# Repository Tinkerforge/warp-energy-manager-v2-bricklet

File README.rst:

WARP Energy Manager Bricklet 2.0
================================

**This Bricklet is currently in development.**

This repository contains the firmware source code and the hardware design
files. The documentation generator configs can be found at
https://github.com/Tinkerforge/generators

.. BEGIN WARP REPOSITORIES (managed block, generated from esp32-firmware/repo_overview.rst - do not edit by hand, run update_repo_overview.py instead)

WARP Repositories
-----------------

This is an overview of all repositories that make up the WARP Charger and
WARP Energy Manager ecosystem.

Please report **any** issue concerning WARP hard- or software in the
`esp32-firmware`_ repository, no matter which repository it originates from.

Software
~~~~~~~~

- `esp32-firmware`_ - Source code of the ESP32 firmware shared between all WARP Chargers and Energy Managers

Libraries used by the firmware:

- `tfjson`_ - SAX style JSON serializer and deserializer
- `tfnetwork`_ - Modbus TCP server and client implementation
- `tfocpp`_ - OCPP 1.6 implementation
- `tftools`_ - Miscellaneous tools and helpers

Remote access:

- `esp32-remote-access`_ - Source code of the my.warp-charger.com remote access server

Documentation, tools and integrations:

- `warp-charger`_ - Source code of (docs.)warp-charger.com and the printed manual, released firmwares, datasheets and documents, as well as some tools and hardware design files
- `api.warp-charger.com`_ - Serves APIs that are used by WARP Chargers to obtain relevant public information like day ahead prices
- `vislog.warp-charger.com`_ - Visualizes WARP Charger logs and EVSE debug protocols
- `dbus-warp-charger`_ - Integrates WARP Chargers into a Victron Energy Venus OS device (e.g. Cerbo GX)

WARP Charger Hardware
~~~~~~~~~~~~~~~~~~~~~~

WARP4 Charger
"""""""""""""

*Current charger generation.*

- `warp-esp32-ethernet-v2-brick`_ - Hardware design files of the WARP ESP32 Ethernet Brick 2.0
- `warp-esp32-ethernet-v2-co-bricklet`_ - Firmware source code of the WARP ESP32 Ethernet 2.0 Co Bricklet (co-processor)
- `evse-v4-bricklet`_ - Hardware design files of the EVSE 4.0 Bricklet (firmware shared with the EVSE 2.0 Bricklet)
- `nfc-bricklet`_ - Firmware source code and hardware design files of the NFC Bricklet

WARP3 Charger
"""""""""""""

- `warp-esp32-ethernet-brick`_ - Hardware design files of the WARP ESP32 Ethernet Brick
- `evse-v3-bricklet`_ - Hardware design files of the EVSE 3.0 Bricklet (firmware shared with the EVSE 2.0 Bricklet)
- `nfc-bricklet`_ - Firmware source code and hardware design files of the NFC Bricklet

WARP2 Charger
"""""""""""""

- `esp32-ethernet-brick`_ - Hardware design files of the ESP32 Ethernet Brick
- `evse-v2-bricklet`_ - Firmware source code and hardware design files of the EVSE 2.0 Bricklet
- `nfc-bricklet`_ - Firmware source code and hardware design files of the NFC Bricklet

WARP1 Charger
"""""""""""""

- `esp32-brick`_ - Hardware design files of the ESP32 Brick
- `evse-bricklet`_ - Firmware source code and hardware design files of the EVSE Bricklet
- `rs485-bricklet`_ - Firmware source code and hardware design files of the RS485 Bricklet

WARP Energy Manager Hardware
~~~~~~~~~~~~~~~~~~~~~~~~~~~~~~

WARP Energy Manager 2.0
"""""""""""""""""""""""

*Current energy manager generation.*

- `esp32-ethernet-brick`_ - Hardware design files of the ESP32 Ethernet Brick
- `warp-energy-manager-v2-bricklet`_ - Firmware source code and hardware design files of the WARP Energy Manager 2.0 Bricklet
- `warp-front-panel-bricklet`_ - Firmware source code and hardware design files of the WARP Front Panel Bricklet

WARP Energy Manager 1.0
"""""""""""""""""""""""

- `esp32-ethernet-brick`_ - Hardware design files of the ESP32 Ethernet Brick
- `warp-energy-manager-bricklet`_ - Firmware source code and hardware design files of the WARP Energy Manager Bricklet

Forked/patched projects
~~~~~~~~~~~~~~~~~~~~~~~~~

- `arduino-esp32`_
- `esp32-arduino-libs`_
- `WireGuard-ESP32-Arduino`_

.. Link targets: One definition per repository, keep in sync with the lists above.

.. _esp32-firmware: https://github.com/Tinkerforge/esp32-firmware
.. _tfjson: https://github.com/Tinkerforge/tfjson
.. _tfnetwork: https://github.com/Tinkerforge/tfnetwork
.. _tfocpp: https://github.com/Tinkerforge/tfocpp
.. _tftools: https://github.com/Tinkerforge/tftools
.. _esp32-remote-access: https://github.com/Tinkerforge/esp32-remote-access
.. _warp-charger: https://github.com/Tinkerforge/warp-charger
.. _api.warp-charger.com: https://github.com/Tinkerforge/api.warp-charger.com
.. _vislog.warp-charger.com: https://github.com/Tinkerforge/vislog.warp-charger.com
.. _dbus-warp-charger: https://github.com/Tinkerforge/dbus-warp-charger
.. _warp-esp32-ethernet-v2-brick: https://github.com/Tinkerforge/warp-esp32-ethernet-v2-brick
.. _warp-esp32-ethernet-v2-co-bricklet: https://github.com/Tinkerforge/warp-esp32-ethernet-v2-co-bricklet
.. _evse-v4-bricklet: https://github.com/Tinkerforge/evse-v4-bricklet
.. _nfc-bricklet: https://github.com/Tinkerforge/nfc-bricklet
.. _warp-esp32-ethernet-brick: https://github.com/Tinkerforge/warp-esp32-ethernet-brick
.. _evse-v3-bricklet: https://github.com/Tinkerforge/evse-v3-bricklet
.. _esp32-ethernet-brick: https://github.com/Tinkerforge/esp32-ethernet-brick
.. _evse-v2-bricklet: https://github.com/Tinkerforge/evse-v2-bricklet
.. _esp32-brick: https://github.com/Tinkerforge/esp32-brick
.. _evse-bricklet: https://github.com/Tinkerforge/evse-bricklet
.. _rs485-bricklet: https://github.com/Tinkerforge/rs485-bricklet
.. _warp-energy-manager-v2-bricklet: https://github.com/Tinkerforge/warp-energy-manager-v2-bricklet
.. _warp-front-panel-bricklet: https://github.com/Tinkerforge/warp-front-panel-bricklet
.. _warp-energy-manager-bricklet: https://github.com/Tinkerforge/warp-energy-manager-bricklet
.. _arduino-esp32: https://github.com/Tinkerforge/arduino-esp32
.. _esp32-arduino-libs: https://github.com/Tinkerforge/esp32-arduino-libs
.. _WireGuard-ESP32-Arduino: https://github.com/Tinkerforge/WireGuard-ESP32-Arduino

.. END WARP REPOSITORIES

Repository Content
------------------

software/:
 * examples/: Examples for all supported languages
 * build/: Compiled files
 * src/: Source code of firmware
 * Makefile: Makefile to build project

hardware/:
 * Contains KiCad project files and additionally schematics as PDF

datasheets/:
 * Contains datasheets for sensors and complex ICs that are used

Hardware
--------

The hardware is designed with the open source EDA Suite KiCad
(http://www.kicad.org). Before you are able to open the files,
you have to install the Tinkerforge kicad-libraries
(https://github.com/Tinkerforge/kicad-libraries). You can either clone
them directly in hardware/ or clone them in a separate folder and
symlink them into hardware/
(ln -s kicad_path/kicad-libraries project_path/hardware). After that you
can open the .pro file in hardware/ with KiCad and from there view and
modify the schematics and the PCB layout.

Software
--------

If you want to do your own Brick/Bricklet firmware development we highly
recommend that you use our build environment setup script and read the
tutorial (https://www.tinkerforge.com/en/doc/Tutorials/Tutorial_Build_Environment/Tutorial.html).

To compile the C code we recommend you to install the newest GNU Arm Embedded
Toolchain (https://launchpad.net/gcc-arm-embedded/+download).
You also need to install bricklib2 (https://github.com/Tinkerforge/bricklib2).

You can either clone it directly in software/src/ or clone it in a
separate folder and symlink it into software/src/
(ln -s bricklib_path/bricklib2 project_path/software/src/). Finally make sure to
have CMake installed (http://www.cmake.org/cmake/resources/software.html).

After that you can build the firmware by invoking make in software/.
The firmware (.zbin) can then be found in software/build/ and uploaded
with brickv (click button "Flashing" on start screen).

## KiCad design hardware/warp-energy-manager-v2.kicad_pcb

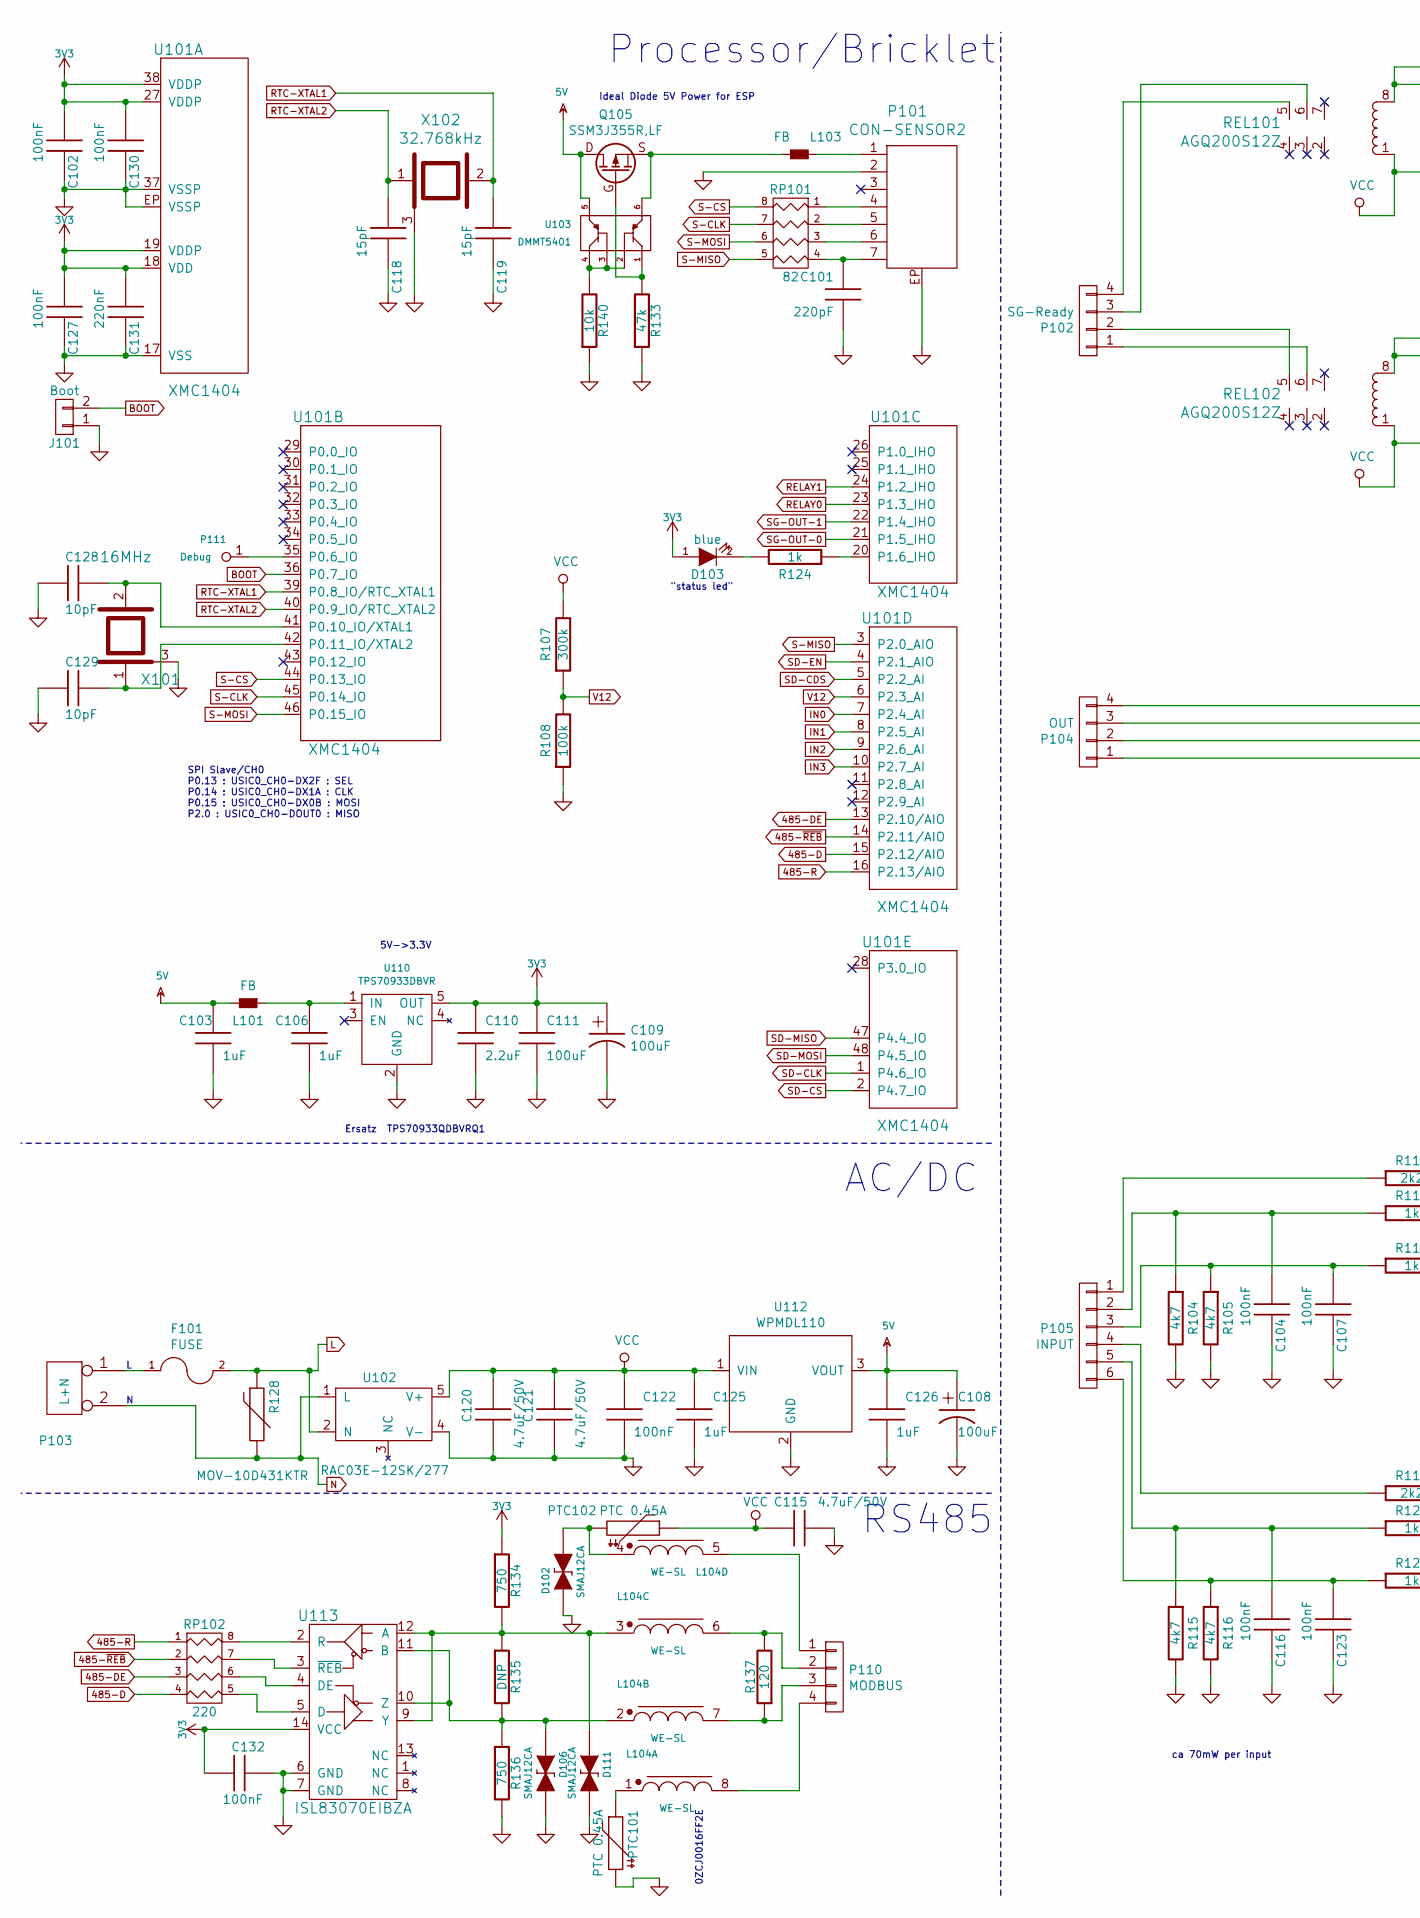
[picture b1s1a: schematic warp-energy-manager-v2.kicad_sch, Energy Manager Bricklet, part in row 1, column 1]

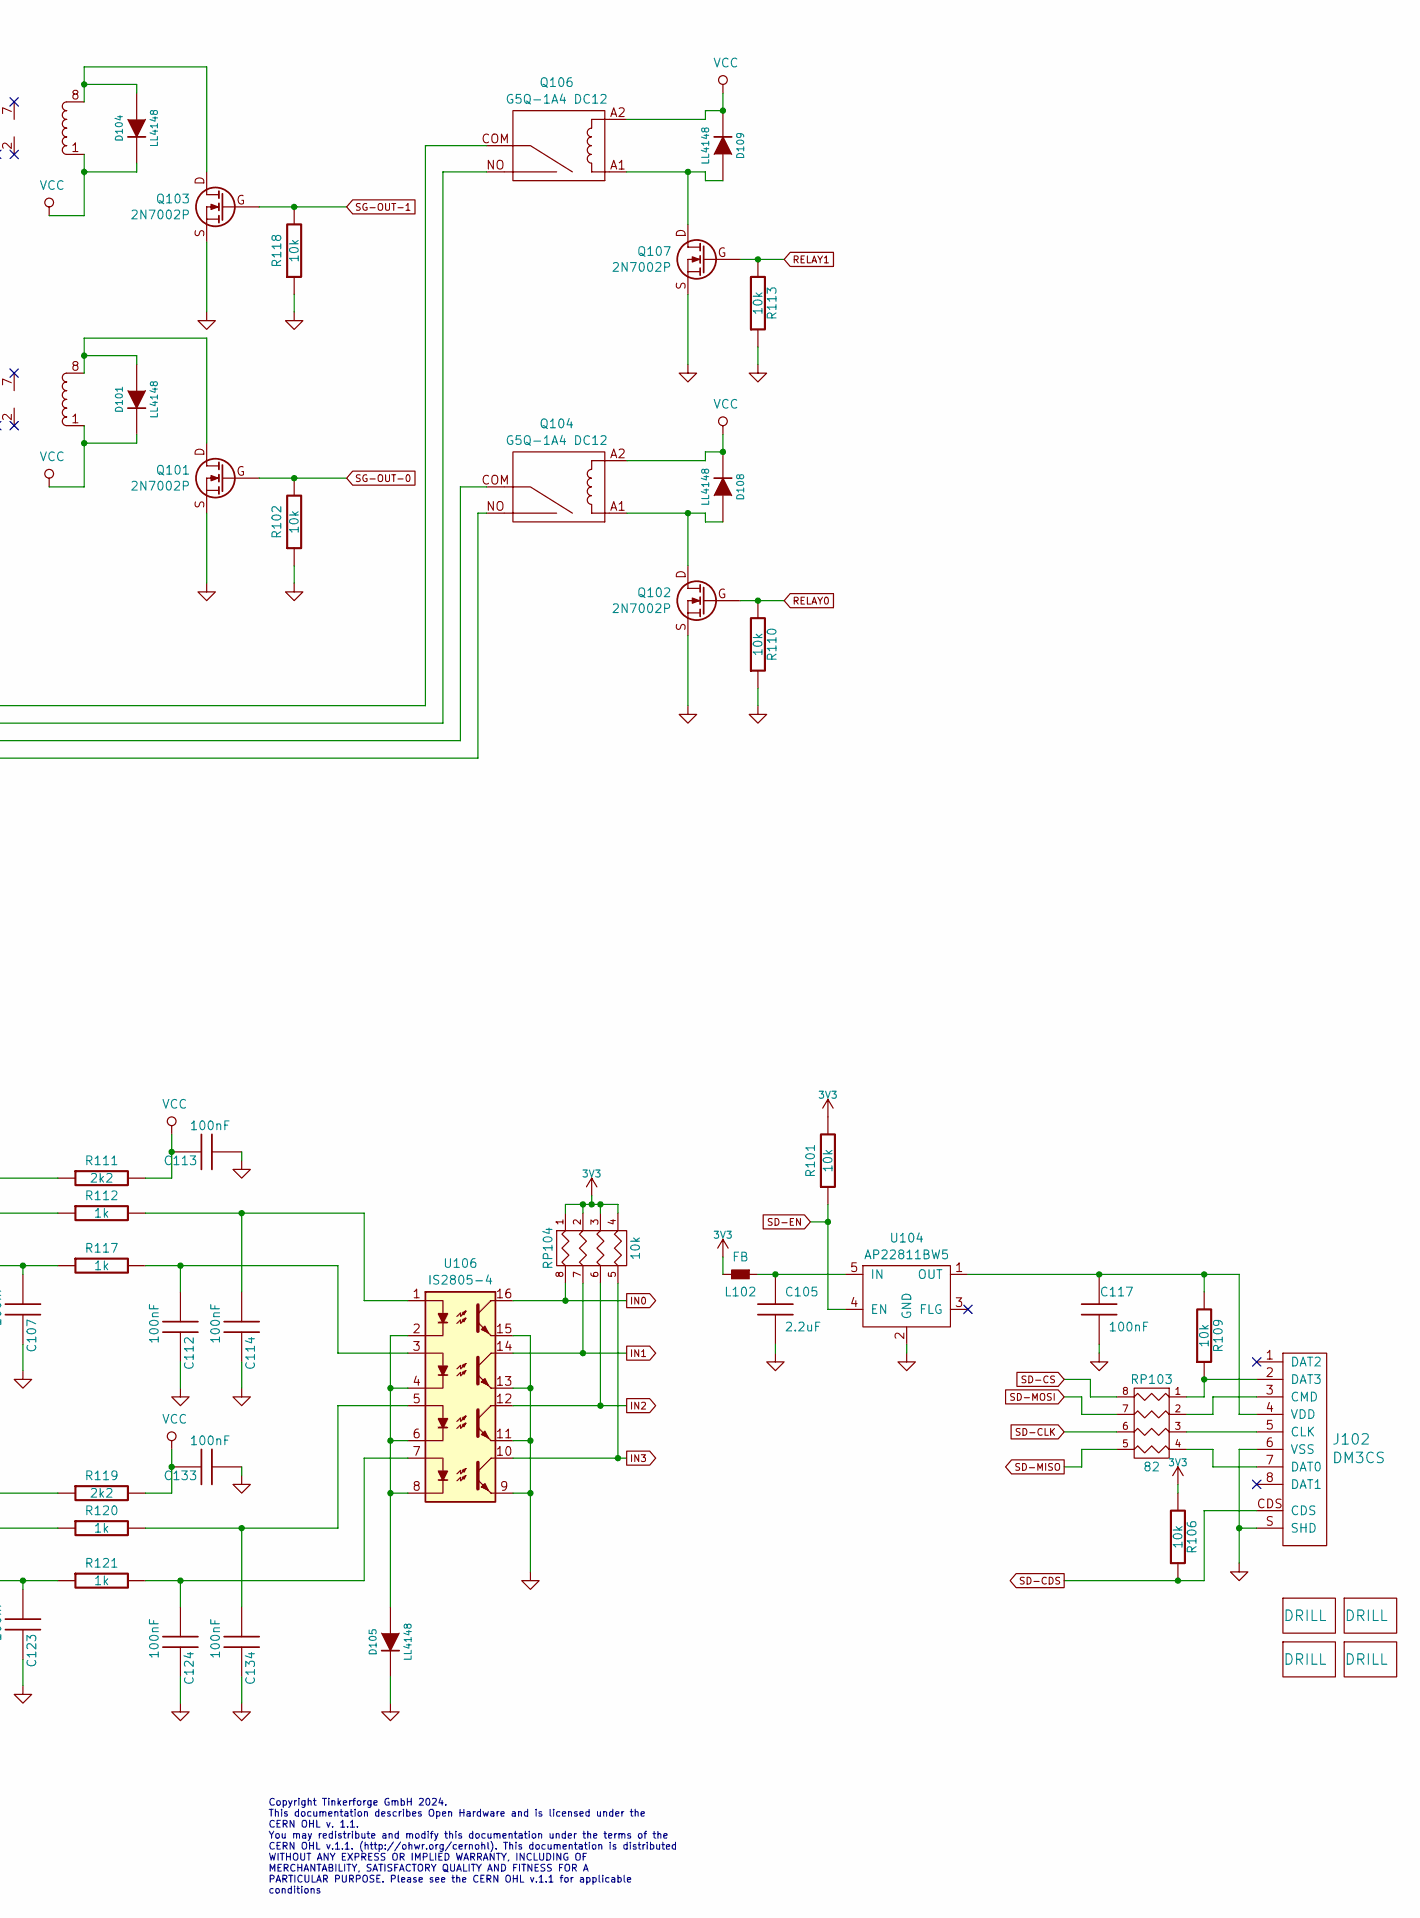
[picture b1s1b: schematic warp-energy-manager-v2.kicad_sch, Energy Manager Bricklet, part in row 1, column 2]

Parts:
A101, A102, A103, A104: DRILL; DRILL_NP_35
C101: 220pF; C0402F
C102, C104, C107, C112, C113, C114, C116, C117, C122, C123, C124, C127, C130, C132, C133, C134: 100nF; C0603F
C103, C106, C125, C126: 1uF; C0603F
C105, C110: 2.2uF; C0603F
C108, C109: 100uF; ELKO_63
C111: 100uF; C1210
C115, C120, C121: 4.7uF/50V; C1206
C118, C119: 15pF; C0603F
C128, C129: 10pF; C0603F
C131: 220nF; C0603F
D101, D104, D105, D108, D109: LL4148; MiniMelf
D102, D106, D111: SMAJ12CA; DO-214AC
D103: blue; D0603F
F101: FUSE; Fuse-Holder-5x20
J101: Boot; SolderJumper
J102: DM3CS; SD-Card-DM3CS
L101, L102, L103: FB; R0603F
L104: WE-SL
P101: CON-SENSOR2; CON-SENSOR2_180
P102: SG-Ready; OQ_4P
P103: L+N; OQ_2P_5mm_230V
P104: OUT; OQ_4P_5mm_230V
P105: INPUT; OQ_6P
P110: MODBUS; OQ_4P
P111: Debug; TSTP_STL
PTC101, PTC102: PTC 0.45A; R1206E
Q101, Q102, Q103, Q107: 2N7002P; SOT23GDS
Q104, Q106: G5Q-1A4 DC12; G5Q-1A
Q105: SSM3J355R,LF; SOT23GDS
R101, R102, R106, R109, R110, R113, R118, R140: 10k; R0603F
R104, R105, R115, R116: 4k7; R0805E
R107: 300k; R0603F
R108: 100k; R0603F
R111, R119: 2k2; R1206E
R112, R117, R120, R121: 1k; R0805E
R124: 1k; R0603F
R128: MOV-10D431KTR; VAR_10mm
R133: 47k; R0603F
R134, R136: 750; R0603F
R135: DNP; R0603F
R137: 120; R0805E
REL101, REL102: AGQ200S12Z; AGQ2X0
RP101, RP103: 82; 4X0402
RP102: 220; 0603X4
RP104: 10k; 4X0603
U101: XMC1404; QFN48-EP2
U102: RAC03E-12SK/277; RAC03E-K277
U103: DMMT5401; SOT26
U104: AP22811BW5; SOT25
U106: IS2805-4; SOIC16_44
U110: TPS70933DBVR; SOT23-5
U112: WPMDL110
U113: ISL83070EIBZA; SOIC-14_3.9x8.7mm_Pitch1.27mm
X101: 16MHz; CRYSTAL_3225
X102: 32.768kHz; AB26TRQ

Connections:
3V3: C102.1, C109.1, C110.1, C111.1, C127.1, C130.1, C131.1, C132.2, D103.1 (A), L102.2, R101.2, R106.2, R134.1, RP104.1, RP104.2, RP104.3, RP104.4, U101.18 (VDD), U101.19 (VDDP), U101.27 (VDDP), U101.38 (VDDP), U110.5 (OUT), U113.14 (VCC)
5V: C103.1, C108.1, C126.1, L101.2, Q105.D, U103.5, U112.3 (VOUT)
485-D: RP102.4, U101.15 (P2.12/AIO)
485-DE: RP102.3, U101.13 (P2.10/AIO)
485-R: RP102.1, U101.16 (P2.13/AIO)
485-~REB: RP102.2, U101.14 (P2.11/AIO)
BOOT: J101.2, U101.36 (P0.7_IO)
GND: C101.2, C102.2, C103.2, C104.2, C105.2, C106.2, C107.2, C108.2, C109.2, C110.2, C111.2, C112.2, C113.1, C114.2, C115.1, C116.2, C117.2, C118.1, C119.1, C120.2, C121.2, C122.2, C123.2, C124.2, C125.2, C126.2, C127.2, C128.2, C129.2, C130.2, C131.2, C132.1, C133.1, C134.2, D102.1 (A), D105.2 (K), D106.2 (K), D111.2 (K), J101.1, J102.6 (VSS), J102.S (SHD), P101.2, P101.EP, PTC101.2, Q101.S, Q102.S, Q103.S, Q107.S, R102.1, R104.2, R105.2, R108.1, R110.1, R113.1, R115.2, R116.2, R118.1, R133.1, R136.2, R140.1, U101.17 (VSS), U101.37 (VSSP), U101.EP (VSSP), U102.4 (V-), U104.2 (GND), U106.9, U106.11, U106.13, U106.15, U110.2 (GND), U112.2 (GND), U113.6 (GND), U113.7 (GND), X101.3, X102.3
IN0: RP104.8 (R1), U101.7 (P2.4_AI), U106.16
IN1: RP104.7 (R2), U101.8 (P2.5_AI), U106.14
IN2: RP104.6 (R3), U101.9 (P2.6_AI), U106.12
IN3: RP104.5 (R4), U101.10 (P2.7_AI), U106.10
L: F101.2, R128.1, U102.2 (N)
N: P103.2 (PM), R128.2, U102.1 (L)
unnamed: C112.1, R117.2, U106.3
unnamed: C114.1, R112.2, U106.1
unnamed: C124.1, R121.2, U106.7
unnamed: C134.1, R120.2, U106.5
unnamed: D101.1 (A), Q101.D, REL102.8
unnamed: D102.2 (K), L104.4, PTC102.2
unnamed: D103.2 (K), R124.2
unnamed: D104.1 (A), Q103.D, REL101.8
unnamed: D105.1 (A), U106.2, U106.4, U106.6, U106.8
unnamed: D106.1 (A), L104.2, R135.2, R136.1, U113.10 (Z), U113.11 (B)
unnamed: D108.1 (A), Q102.D, Q104.A1
unnamed: D109.1 (A), Q106.A1, Q107.D
unnamed: D111.1 (A), L104.3, R134.2, R135.1, U113.9 (Y), U113.12 (A)
unnamed: J102.5 (CLK), RP103.3
unnamed: J102.3 (CMD), RP103.2
unnamed: J102.7 (DAT0), RP103.4
unnamed: J102.2 (DAT3), R109.1, RP103.1
unnamed: C117.1, J102.4 (VDD), R109.2, U104.1 (OUT)
unnamed: L103.1, Q105.S, U103.6
unnamed: L103.2, P101.1
unnamed: L104.1, PTC101.1
unnamed: P102.1, REL102.6
unnamed: P102.2, REL102.5
unnamed: P102.3, REL101.6
unnamed: P102.4, REL101.5
unnamed: F101.1, P103.1
unnamed: P104.1, Q104.NO
unnamed: P104.2, Q104.COM
unnamed: P104.3, Q106.NO
unnamed: P104.4, Q106.COM
unnamed: P105.1, R111.1
unnamed: C104.1, P105.2, R104.1, R112.1
unnamed: C107.1, P105.3, R105.1, R117.1
unnamed: P105.4, R119.1
unnamed: C116.1, P105.5, R115.1, R120.1
unnamed: C123.1, P105.6, R116.1, R121.1
unnamed: L104.5, P110.1
unnamed: L104.6, P110.2, R137.2
unnamed: L104.7, P110.3, R137.1
unnamed: L104.8, P110.4
unnamed: Q105.G, R133.2, U103.1
unnamed: R140.2, U103.2, U103.3, U103.4
unnamed: P101.4, RP101.1
unnamed: P101.5, RP101.2
unnamed: P101.6, RP101.3
unnamed: C101.1, P101.7, RP101.4
unnamed: RP102.8 (R1), U113.2 (R)
unnamed: RP102.7 (R2), U113.3 (~REB)
unnamed: RP102.6 (R3), U113.4 (DE)
unnamed: RP102.5 (R4), U113.5 (D)
unnamed: P111.1, U101.35 (P0.6_IO)
unnamed: C128.1, U101.41 (P0.10_IO/XTAL1), X101.2
unnamed: C129.1, U101.42 (P0.11_IO/XTAL2), X101.1
unnamed: R124.1, U101.20 (P1.6_IHO)
unnamed: C105.1, L102.1, U104.5 (IN)
unnamed: C106.1, L101.1, U110.1 (IN)
RELAY0: Q102.G, R110.2, U101.23 (P1.3_IHO)
RELAY1: Q107.G, R113.2, U101.24 (P1.2_IHO)
RTC-XTAL1: C119.2, U101.39 (P0.8_IO/RTC_XTAL1), X102.2
RTC-XTAL2: C118.2, U101.40 (P0.9_IO/RTC_XTAL2), X102.1
S-CLK: RP101.7 (R2), U101.45 (P0.14_IO)
S-CS: RP101.8 (R1), U101.44 (P0.13_IO)
S-MISO: RP101.5 (R4), U101.3 (P2.0_AIO)
S-MOSI: RP101.6 (R3), U101.46 (P0.15_IO)
SD-CDS: J102.CDS, R106.1, U101.5 (P2.2_AI)
SD-CLK: RP103.6 (R3), U101.1 (P4.6_IO)
SD-CS: RP103.8 (R1), U101.2 (P4.7_IO)
SD-EN: R101.1, U101.4 (P2.1_AIO), U104.4 (EN)
SD-MISO: RP103.5 (R4), U101.47 (P4.4_IO)
SD-MOSI: RP103.7 (R2), U101.48 (P4.5_IO)
SG-OUT-0: Q101.G, R102.2, U101.21 (P1.5_IHO)
SG-OUT-1: Q103.G, R118.2, U101.22 (P1.4_IHO)
V12: R107.1, R108.2, U101.6 (P2.3_AI)
VCC: C113.2, C115.2, C120.1, C121.1, C122.1, C125.1, C133.2, D101.2 (K), D104.2 (K), D108.2 (K), D109.2 (K), PTC102.1, Q104.A2, Q106.A2, R107.2, R111.2, R119.2, REL101.1, REL102.1, U102.5 (V+), U112.1 (VIN)

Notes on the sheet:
ca 70mW per input
SPI Slave/CH0 P0.13 : USIC0_CH0-DX2F : SEL P0.14 : USIC0_CH0-DX1A : CLK P0.15 : USIC0_CH0-DX0B : MOSI P2.0 : USIC0_CH0-DOUT0 : MISO
Ersatz TPS70933QDBVRQ1
Processor/Bricklet
"status led"
0ZCJ0016FF2E
RS485
5V->3.3V
Copyright Tinkerforge GmbH 2024. This documentation describes Open Hardware and is licensed under the CERN OHL v. 1.1. You may redistribute and modify this documentation under the terms of the CERN OHL v.1.1. (http://ohwr.org/cernohl). This documentation is distributed WITHOUT ANY EXPRESS OR IMPLIE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
AC/DC
Ideal Diode 5V Power for ESP

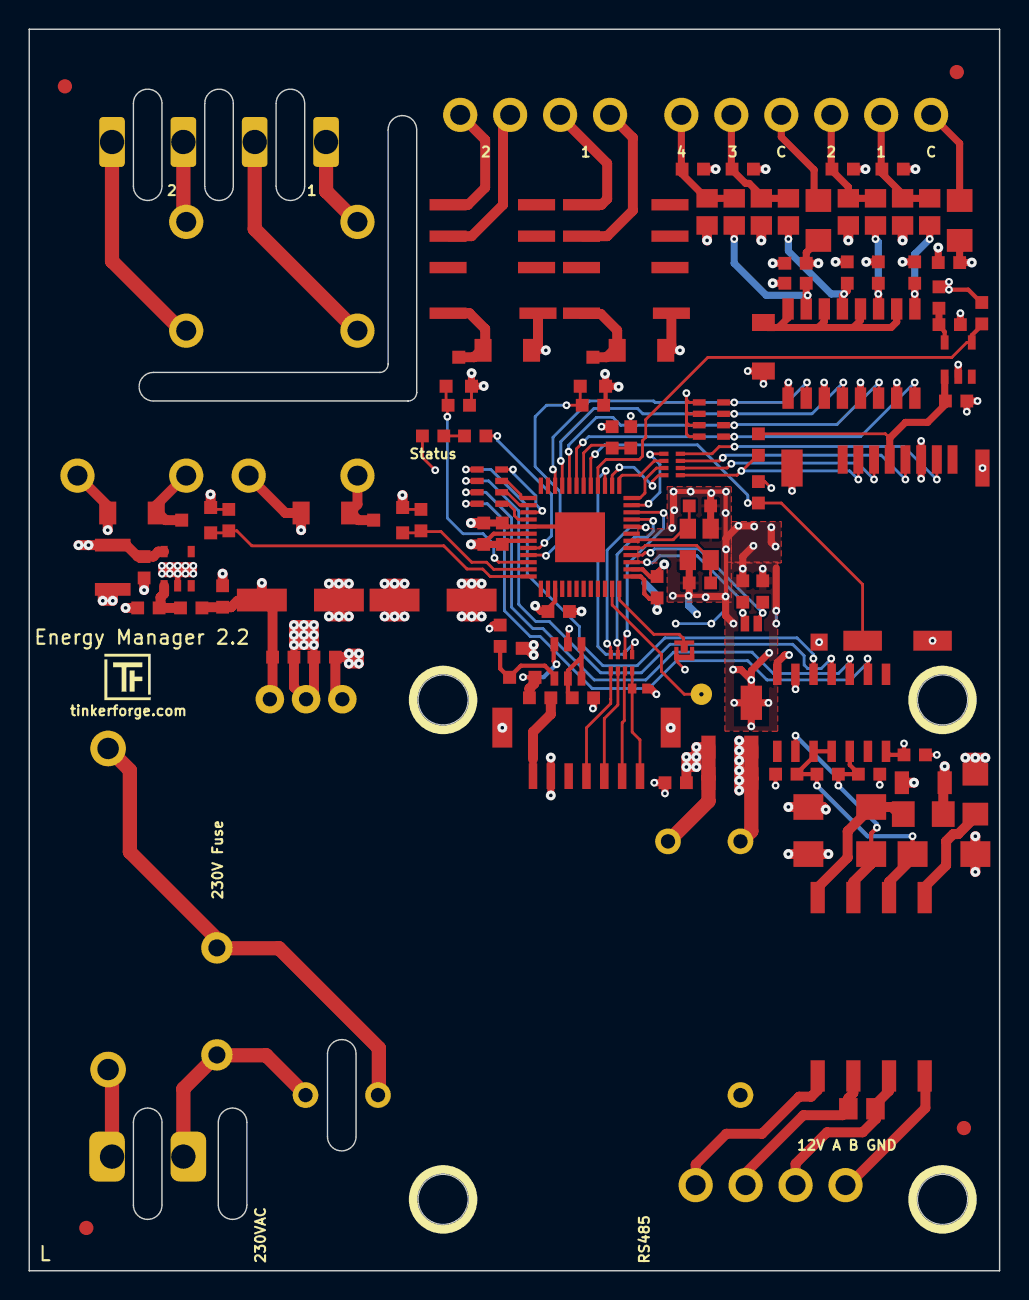
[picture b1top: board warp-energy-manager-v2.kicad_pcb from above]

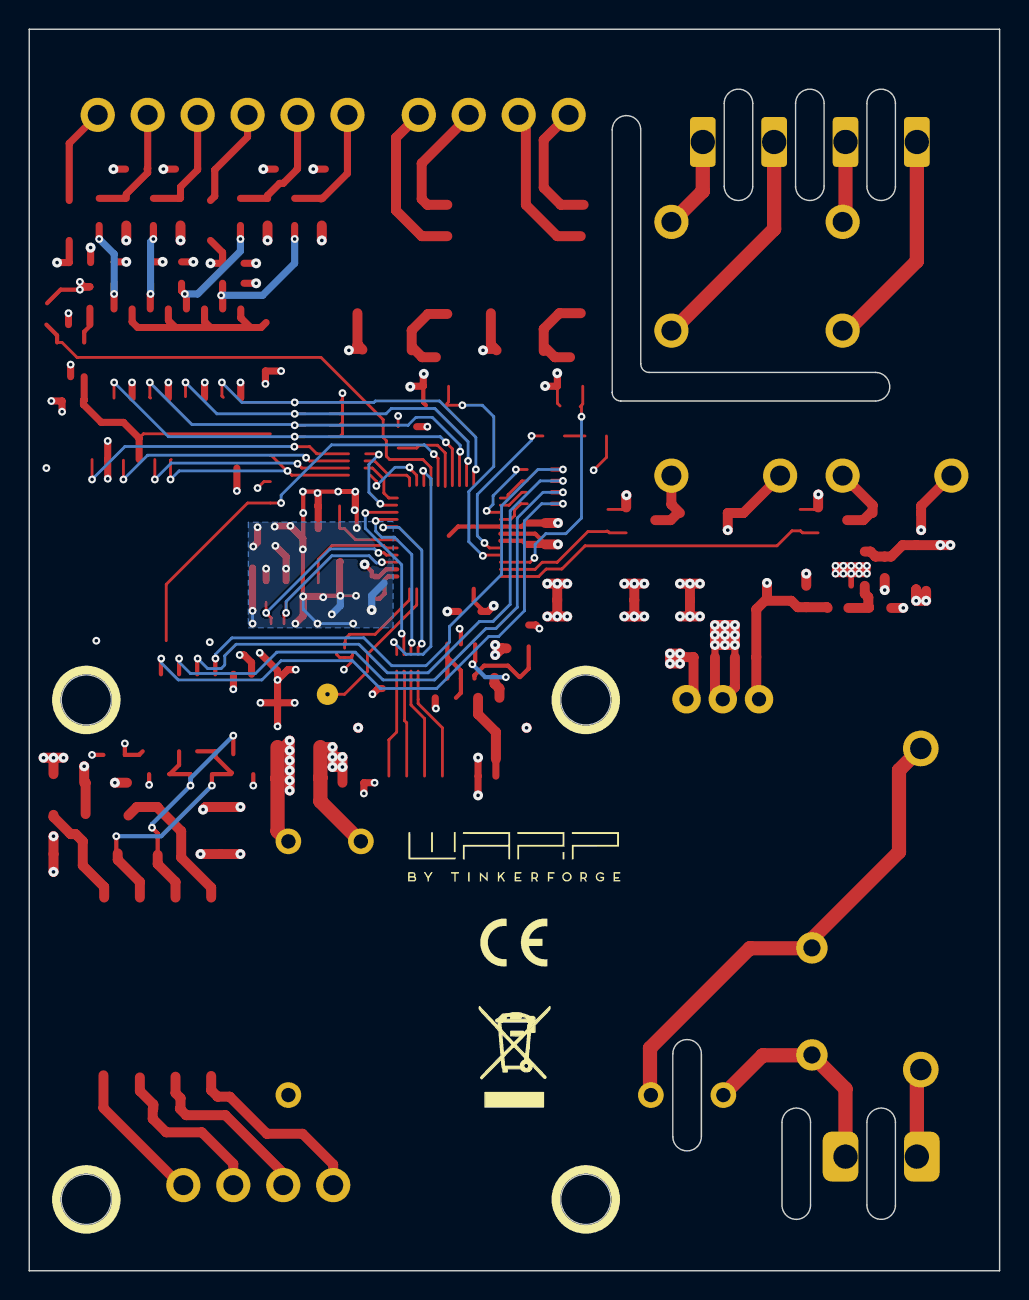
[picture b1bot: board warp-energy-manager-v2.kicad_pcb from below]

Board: 4 copper layers, 68.0 x 87.0 mm, 119 parts (2 on the bottom side), 88 nets.

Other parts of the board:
Fiducial_Mark: VAL**; Fiducial_Mark
Fiducial_Mark#2, Fiducial_Mark#3, Fiducial_Mark#4: VAL**; Fiducial_Mark
VAL: WEEE_7mm
VAL#2: CE_5mm

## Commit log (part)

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2024-06-13 initial commit of autogenerated bricklet firmware stub
2024-06-17 Remove LED functions (will be in WARP Front Panel Bricklet)
2024-06-17 Split output into sg ready and relay output
2024-06-17 first hardware mockup
2024-06-20 routing started
2024-06-20 fix schematic drcs
2024-06-21 fully routed
2024-06-21 all bugs fixed
2024-06-21 prototype version
2024-06-24 add 3d models
2024-06-24 add descriptions
2024-07-01 add schematic as pdf
2024-07-01 Add io test script
2024-07-01 Add initial stub firmware
    this is mostly copied stuff from WEM 1.0
2024-07-01 fix relay1 control function
2024-07-17 add version 2.1: fix varistor space, fix status led
2024-07-18 hardware version 2.2 : changed connector overhang by +1,5mm
2024-09-02 Move everything that is common between WEM 1/2 to bricklib2
2024-09-02 Implement API
    This is mostly the same between WEM 1.0 and 2.0
2024-09-02 Add support for price data
    sd write/read changes in bricklib2
2024-09-02 Move EEPROM and voltage code to bricklib
2024-09-02 Add and implement all data getter
2024-09-11 Fix return value of get_all_data_1
2024-09-13 change varistor value
2024-09-13 Change default for all relays to low
2024-09-14 Fix LED pin
2024-09-17 inputs are active low
2024-09-17 Fix configuration for 12V input voltage measurement
2024-09-17 Remove unused code
2024-09-17 Use new cb length defines (from bricklib)
2024-09-18 Fix order of output pins
2024-09-18 Change output setter to accept channel
2024-09-27 Use 16bit for flags
2024-10-04 add logos
2024-10-22 Update bindings
2024-10-22 Add more test scripts
2024-10-25 Add support for status parameter in get_data_storage
2024-10-28 Initialize data storage before sd card
2024-11-13 Update test
2024-12-06 Turn debugging off by default
2024-12-06 Add date and ref for 2.0.0
2025-02-05 Make sure first set_data_storage call is always written to SD card
2025-02-05 Add ref for 2.0.1
2025-03-28 Update version and changelog
2025-03-28 Add ref for 2.0.2
2025-04-03 Increase data storge pages from 3 to 5 (through bricklib2)
2025-04-03 Add ref for 2.0.3
2025-07-16 README: Add repo overview.
2025-09-14 Add support for DMED341MID7ER, DSZ16DZE, WM3M4C and use restructured meter code
    see bricklib2 for implementation
2025-09-16 Rename MeterRegisterType to use the same name as in esp32 firmware
2025-09-16 Add libm and free some RAM to allow sqrt use in bricklib2
2025-09-21 Make cmake version compatible to new build environment
2025-09-21 Add support for dynamic length meter values
2025-10-02 Fix -Wextra warnings and add new warning flags introduced in EVSE V2
2025-10-02 Add -Wsign-conversion warning
2025-10-02 Improve comment
2025-11-03 Add ref and release date for 2.0.4
2026-05-13 Add support for WM3M4, update changelog
2026-05-13 Add ref for 2.0.5

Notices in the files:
hardware/warp-energy-manager-v2.kicad_pcb:
Licensed under CERN OHL v.1.1
Copyright (©) 2024, B.Nordmeyer
